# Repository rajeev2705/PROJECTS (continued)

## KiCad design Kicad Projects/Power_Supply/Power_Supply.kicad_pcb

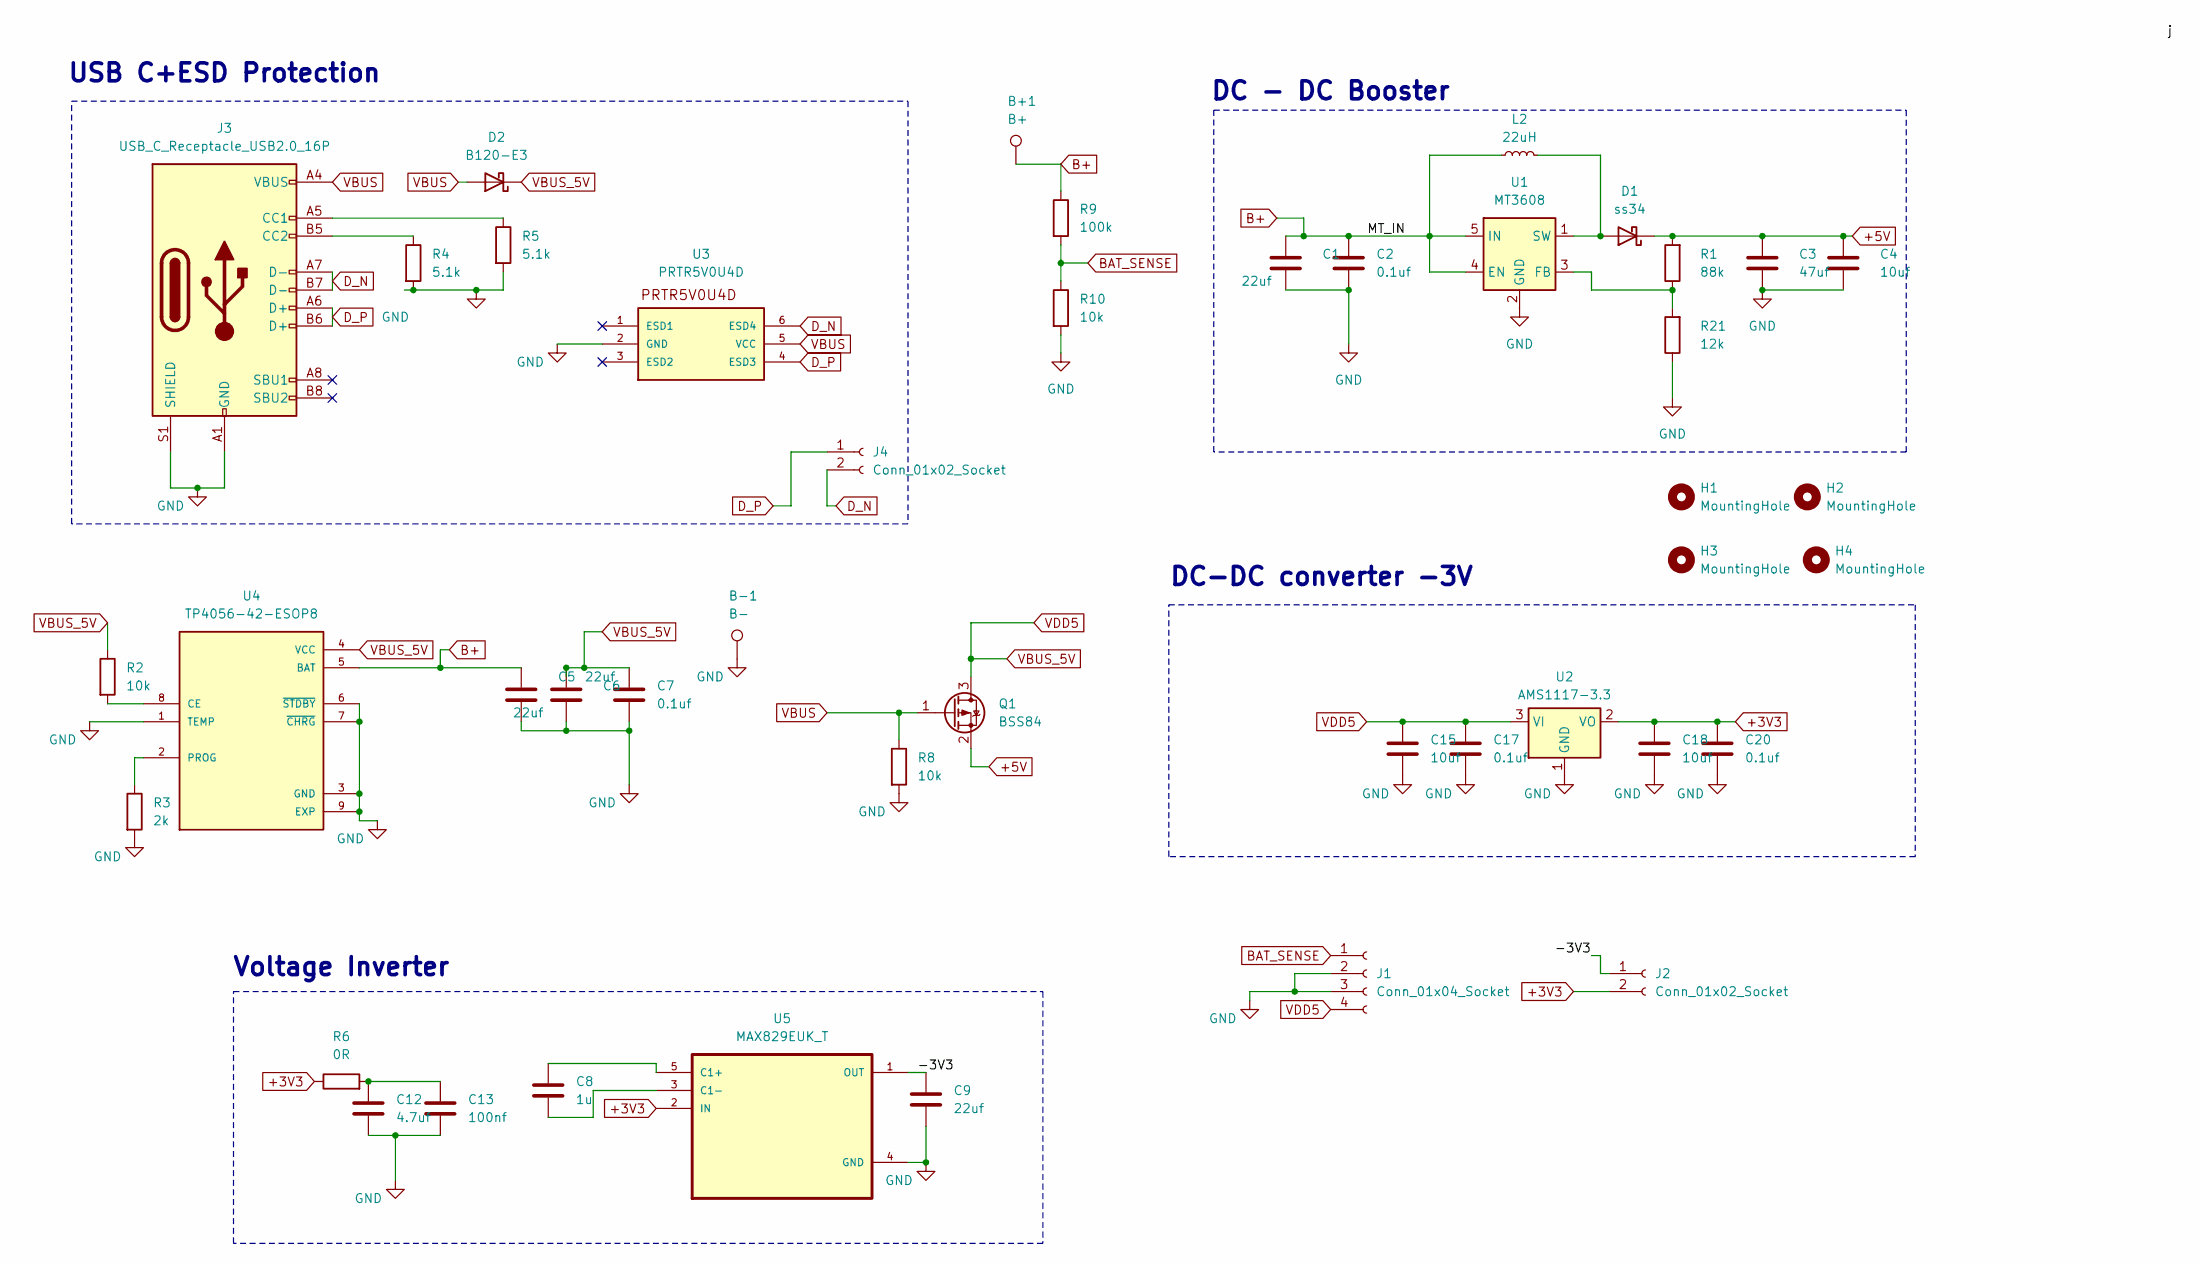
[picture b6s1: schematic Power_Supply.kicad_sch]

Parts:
B+1: B+; TestPoint_Loop_D2.54mm_Drill1.5mm_Beaded
B-1: B-; TestPoint_Loop_D2.54mm_Drill1.5mm_Beaded
C1, C5, C6, C9: 22uf; C_0805_2012Metric_Pad1.18x1.45mm_HandSolder
C2, C7, C17, C20: 0.1uf; C_0805_2012Metric_Pad1.18x1.45mm_HandSolder
C3: 47uf; C_0805_2012Metric_Pad1.18x1.45mm_HandSolder
C4, C15, C18: 10uf; C_0805_2012Metric_Pad1.18x1.45mm_HandSolder
C8: 1u; C_0805_2012Metric_Pad1.18x1.45mm_HandSolder
C12: 4.7uf; C_0805_2012Metric_Pad1.18x1.45mm_HandSolder
C13: 100nf; C_0805_2012Metric_Pad1.18x1.45mm_HandSolder
D1: ss34; D_SMA
D2: B120-E3; D_SMA
H1, H2, H3, H4: MountingHole; MountingHole_2.5mm
J1: Conn_01x04_Socket; PinSocket_1x04_P2.54mm_Vertical
J2, J4: Conn_01x02_Socket; PinSocket_1x02_P2.54mm_Vertical
J3: USB_C_Receptacle_USB2.0_16P; USB_C_Receptacle_HRO_TYPE-C-31-M-12
L2: 22uH; L_TDK_SLF10165
Q1: BSS84; SOT-23
R1: 88k; R_0805_2012Metric_Pad1.20x1.40mm_HandSolder
R2, R8, R10: 10k; R_0805_2012Metric_Pad1.20x1.40mm_HandSolder
R3: 2k; R_0805_2012Metric_Pad1.20x1.40mm_HandSolder
R4, R5: 5.1k; R_0805_2012Metric_Pad1.20x1.40mm_HandSolder
R6: 0R; R_0805_2012Metric_Pad1.20x1.40mm_HandSolder
R9: 100k; R_0805_2012Metric_Pad1.20x1.40mm_HandSolder
R21: 12k; R_0805_2012Metric_Pad1.20x1.40mm_HandSolder
U1: MT3608; SOT-23-6
U2: AMS1117-3.3; SOT-223-3_TabPin2
U3: PRTR5V0U4D; ROHM_SOT-457_ClockwisePinNumbering
U4: TP4056-42-ESOP8; SOIC127P600X175-9N; PARTREV NA
U5: MAX829EUK_T; SOT95P280X145-5N

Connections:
+3V3: C18.1, C20.1, J2.2, R6.1, U2.2 (VO), U5.2 (IN)
+5V: C3.1, C4.1, D1.1 (K), Q1.2 (S), R1.2
/-3V3: C9.1, J2.1, U5.1 (OUT)
B+: B+1.1, C1.1, C2.1, C5.1, L2.2, R9.1, U1.4 (EN), U1.5 (IN), U4.5 (BAT)
BAT_SENSE: J1.1, R9.2, R10.1
D_N: J3.A7 (D-), J3.B7 (D-), J4.2, U3.6 (ESD4)
D_P: J3.A6 (D+), J3.B6 (D+), J4.1, U3.4 (ESD3)
GND: B-1.1, C1.2, C2.2, C3.2, C4.2, C5.2, C6.2, C7.2, C9.2, C12.2, C13.2, C15.2, C17.2, C18.2, C20.2, J1.2, J1.3, J3.A1 (GND), J3.A12 (GND), J3.B1 (GND), J3.B12 (GND), J3.S1 (SHIELD), R3.2, R4.2, R5.2, R8.2, R10.2, R21.1, U1.2 (GND), U2.1 (GND), U3.2 (GND), U4.1 (TEMP), U4.3 (GND), U4.6 (~STDBY), U4.7 (~CHRG), U4.9 (EXP), U5.4 (GND)
unnamed: C12.1, C13.1, R6.2
unnamed: D1.2 (A), L2.1, U1.1 (SW)
unnamed: J3.A5 (CC1), R5.1
unnamed: J3.B5 (CC2), R4.1
unnamed: R1.1, R21.2, U1.3 (FB)
unnamed: R2.2, U4.8 (CE)
unnamed: R3.1, U4.2 (PROG)
unnamed: C8.1, U5.5 (C1+)
unnamed: C8.2, U5.3 (C1-)
VBUS: D2.2 (A), J3.A4 (VBUS), J3.A9 (VBUS), J3.B4 (VBUS), J3.B9 (VBUS), Q1.1 (G), R8.1, U3.5 (VCC)
VBUS_5V: C6.1, C7.1, C15.1, C17.1, D2.1 (K), J1.4, Q1.3 (D), R2.1, U2.3 (VI), U4.4 (VCC)

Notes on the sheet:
DC - DC Booster
USB C+ESD Protection
DC-DC converter -3V
Voltage Inverter

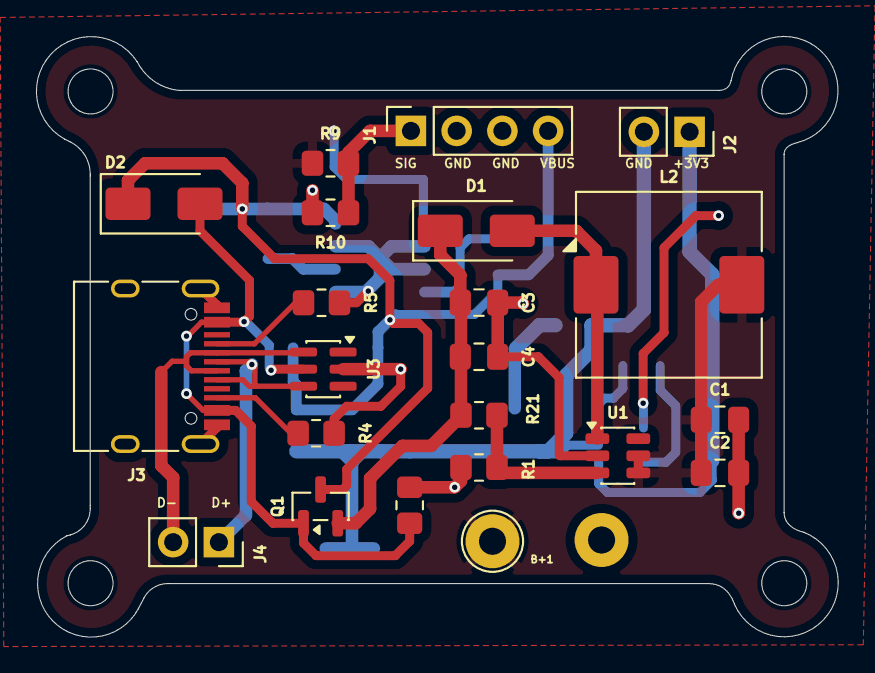
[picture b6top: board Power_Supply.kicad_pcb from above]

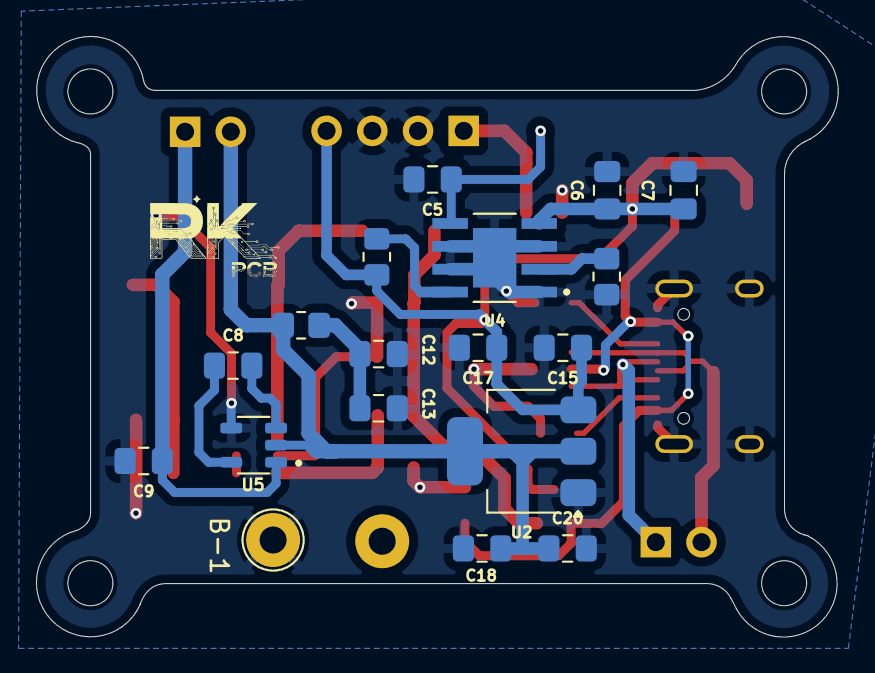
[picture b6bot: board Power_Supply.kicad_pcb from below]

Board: 2 copper layers, 44.5 x 33.4 mm, 44 parts (18 on the bottom side), 19 nets.

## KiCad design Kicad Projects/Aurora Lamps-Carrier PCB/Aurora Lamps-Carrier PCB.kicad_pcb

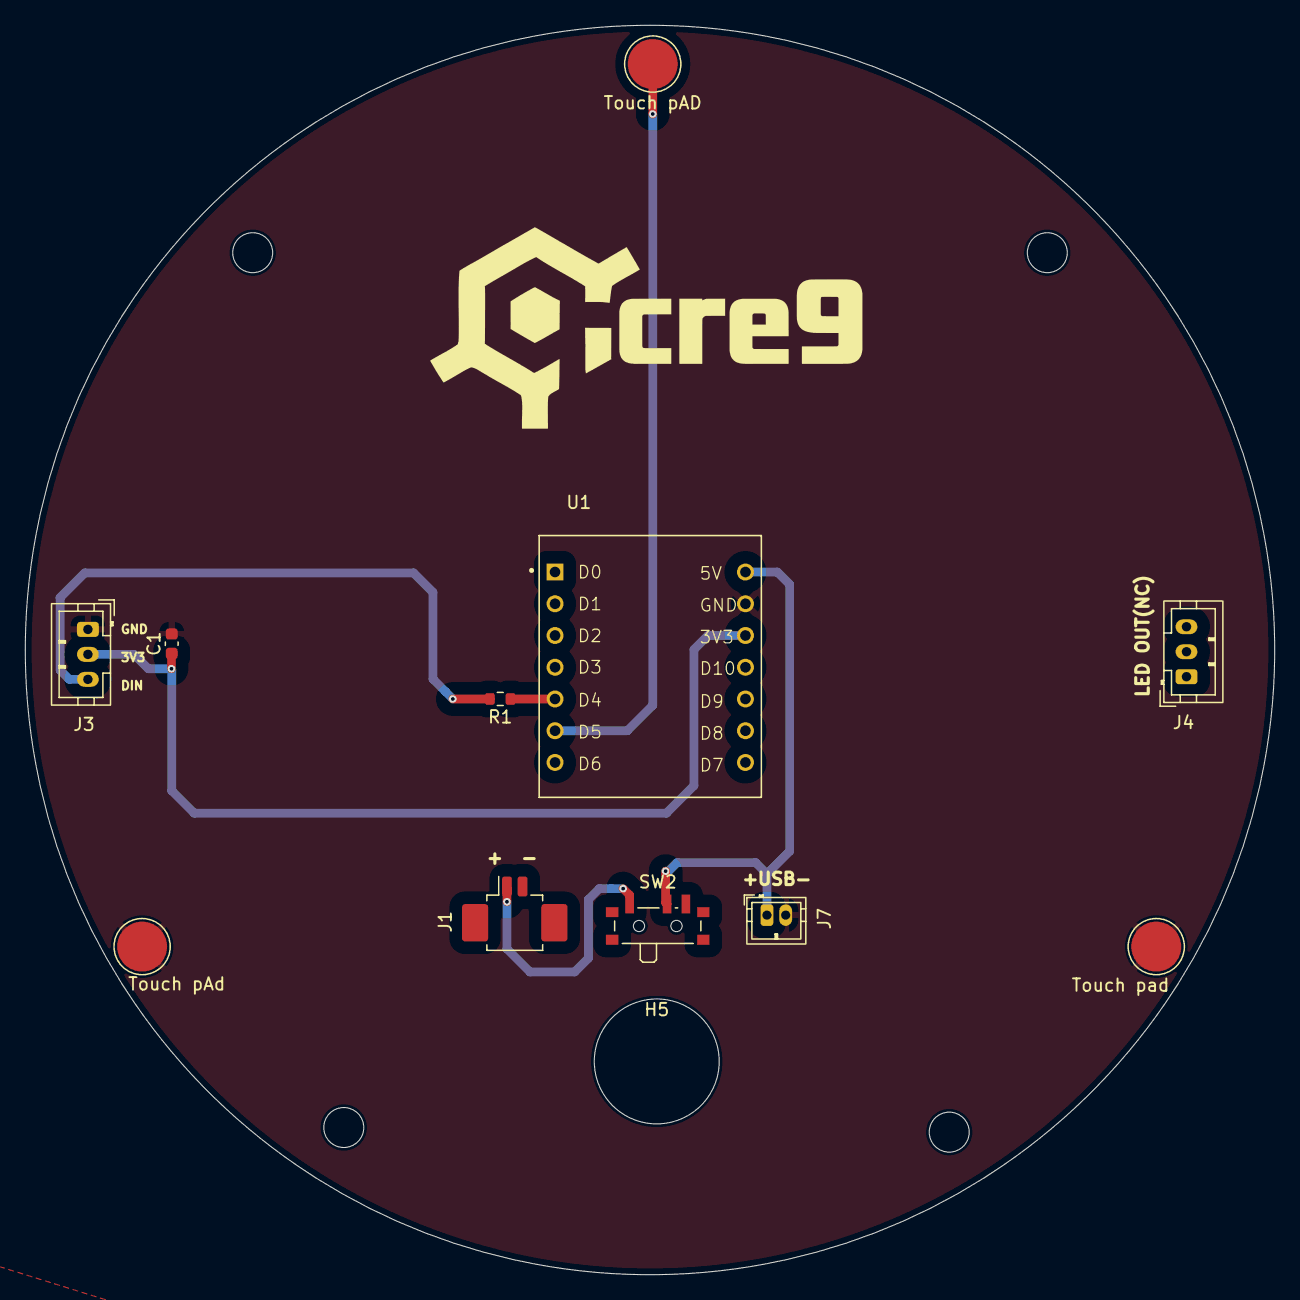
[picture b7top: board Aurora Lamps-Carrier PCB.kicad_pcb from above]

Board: 2 copper layers, 100.0 x 100.0 mm, 16 parts (0 on the bottom side), 7 nets.

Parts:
C1: 100nf; C_0603_1608Metric
H1, H2, H3, H4, H5: MountingHole; MountingHole_3.2mm_M3
J1: BATTERY; Molex_PicoBlade_53261-0271_1x02-1MP_P1.25mm_Horizontal
J2: Touch pAD; TestPoint_Pad_D4.0mm
J3: LED Connector; JST_PH_B3B-PH-K_1x03_P2.00mm_Vertical
J4: led ring out; JST_PH_B3B-PH-K_1x03_P2.00mm_Vertical
J5: Touch pad; TestPoint_Pad_D4.0mm
J6: Touch pAd; TestPoint_Pad_D4.0mm
J7: USBPower EXt; JST_ZH_B2B-ZR_1x02_P1.50mm_Vertical
R1: 330R; R_0603_1608Metric
SW2: SW_SPDT; SW_SPDT_PCM12
U1: XIAO_ESP32S3; MODULE_XIAO_ESP32C3

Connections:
B+: J1.1, SW2.1 (A)
BAT+: J7.1, SW2.2 (B), U1.14 (VUSB)
GND: C1.2, J3.1, J5.1, J6.1, J7.2, U1.13 (GND)
LED_DATA: R1.1, U1.5 (D4)
MCU_3V3: C1.1, J3.2, U1.12 (VCC_3V3)
unnamed: J3.3, R1.2
TOUCH: J2.1, U1.6 (D5)

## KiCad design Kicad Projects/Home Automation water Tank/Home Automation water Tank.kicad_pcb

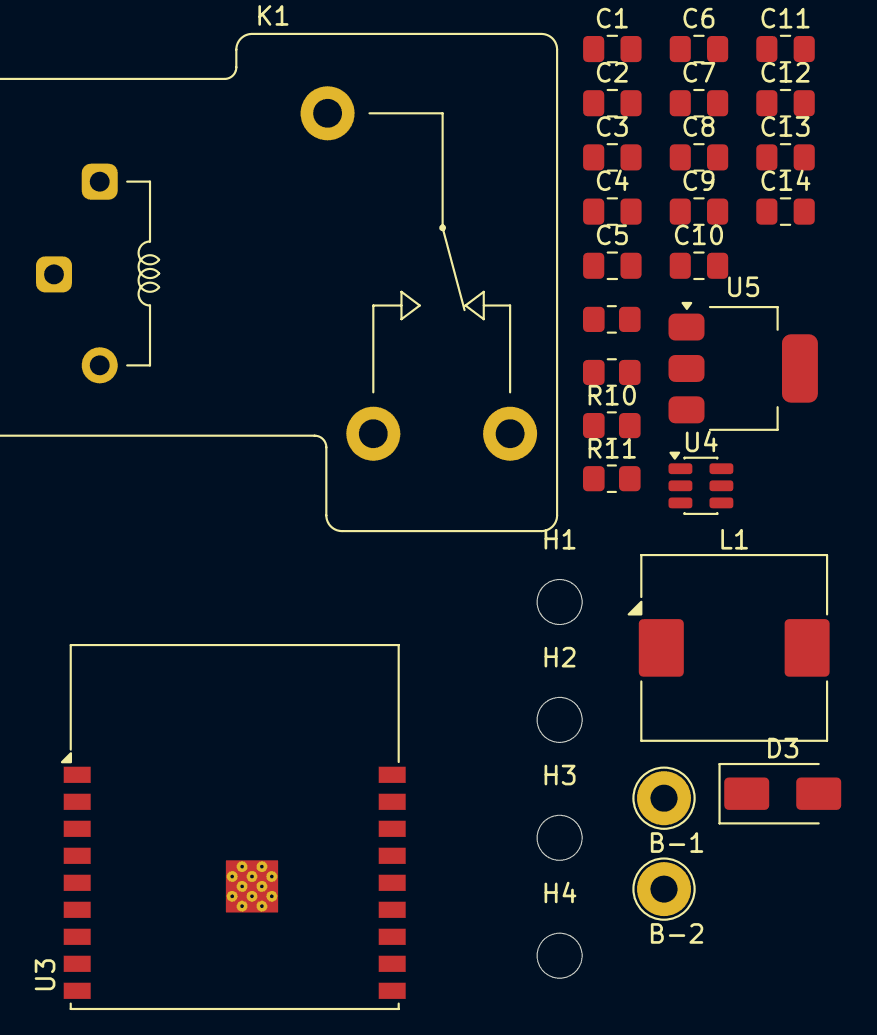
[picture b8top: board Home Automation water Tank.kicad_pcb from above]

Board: 2 copper layers, 30 parts (0 on the bottom side), 8 nets, no tracks yet.

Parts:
B-1: B-; TestPoint_Loop_D2.54mm_Drill1.5mm_Beaded
B-2: B+; TestPoint_Loop_D2.54mm_Drill1.5mm_Beaded
C1, C2, C5: 22uf; C_0805_2012Metric_Pad1.18x1.45mm_HandSolder
C3, C7: 0.1uf; C_0805_2012Metric_Pad1.18x1.45mm_HandSolder
C4, C8, C9, C12, C13: 47uf; C_0805_2012Metric_Pad1.18x1.45mm_HandSolder
C6, C10, C11, C14: 10uf; C_0805_2012Metric_Pad1.18x1.45mm_HandSolder
D3: ss34; D_SMA
H1, H2, H3, H4: MountingHole; MountingHole_2.5mm
K1: RAYEX-L90S; Relay_SPDT_RAYEX-L90S
L1: 22uH; L_TDK_SLF10165
R6: 10k; R_0805_2012Metric_Pad1.20x1.40mm_HandSolder
R7: 2k; R_0805_2012Metric_Pad1.20x1.40mm_HandSolder
R10: 88k; R_0805_2012Metric_Pad1.20x1.40mm_HandSolder
R11: 12k; R_0805_2012Metric_Pad1.20x1.40mm_HandSolder
U3: ESP32-C3-WROOM-02
U4: MT3608; SOT-23-6
U5: AMS1117-3.3; SOT-223-3_TabPin2

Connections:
+3V3: C4.1, C6.1, C13.1, C14.1, U3.1 (3V3), U5.2 (VO)
+6V: C9.1, C10.1, C11.1, C12.1, D3.1 (K), R10.2, U5.3 (VI)
/MCU_EN: C8.2, U3.2 (EN)
B+: B-2.1, C1.1, C5.1, C7.1, L1.2, U4.4 (EN), U4.5 (IN)
GND: B-1.1, C1.2, C2.2, C3.2, C4.2, C5.2, C6.2, C7.2, C8.1, C9.2, C10.2, C11.2, C12.2, C13.2, C14.2, R7.2, R11.1, U3.9 (GND), U3.19 (GND), U4.2 (GND), U5.1 (GND)
unnamed: D3.2 (A), L1.1, U4.1 (SW)
unnamed: R10.1, R11.2, U4.3 (FB)
USB_5V: C2.1, C3.1, R6.1

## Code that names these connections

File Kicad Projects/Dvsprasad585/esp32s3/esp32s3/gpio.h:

/*----------------------------------------------------------------
 *
 * gpio.h
 *
 * Header file for GPIO functions
 * VSKTarget - ESP32-S3 Port (Rev 6.2)
 *
 * ESP32-S3-WROOM-1 Pin Mapping
 * Based on freETarget v5.2 architecture
 *
 * FULL SIGNAL CHAIN (Rev 6.2):
 *   - Filter network (10K + 10nF slope comp) on main board
 *   - 2x LM339 quad comparators on main board
 *   - 4x 74HC74 D flip-flop RUN latches on main board
 *   - ESP32-S3 ISR captures comparator output timestamps
 *   - PCNT-equivalent timing via esp_timer_get_time()
 *   - Sensor daughter boards: Piezo + OPA1641 only
 *   - A0505XT-1WR3-TR isolated ±5V for analog
 *
 * Signal Chain:
 *   Daughter Board: Piezo → OPA1641 amp → analog out via FRC
 *   Main Board: FRC → RC Filter → LM339 (vs VREF) → 74HC74 latch
 *               LM339 output also → ESP32-S3 GPIO ISR (timing)
 *               74HC74 Q → ESP32-S3 GPIO (RUN status)
 *
 *---------------------------------------------------------------*/
#ifndef _GPIO_H_
#define _GPIO_H_

#include "driver/pulse_cnt.h"

/*
 * Global functions
 */
void init_gpio(void);
void init_pcnt(void);
void arm_timers(void);
void clear_running(void);
unsigned int is_running(void);
void set_LED(int state_RDY, int state_X, int state_Y);
unsigned int read_DIP(unsigned int dip_mask);
void stop_timers(void);
void trip_timers(void);
bool read_in(unsigned int port);
void read_timers(unsigned int* timer_counts);
void drive_paper(void);
void enable_face_interrupt();
void disable_face_interrupt(void);
void enable_sensor_interrupt();
void disable_sensor_interrupt(void);
void multifunction_init(void);
void multifunction_switch(void);
void multifunction_display(void);
void multifunction_wait_open(void);
void output_to_all(char* s);
void char_to_all(char ch);
void digital_test(void);
void paper_on_off(bool on);
void rapid_green(unsigned int state);
void rapid_red(unsigned int state);
char get_all(void);
char aux_spool_read(void);
int  aux_spool_available(void);
void aux_spool_put(char ch);
char json_spool_read(void);
int  json_spool_available(void);
void json_spool_put(char ch);
void set_vref(unsigned int millivolts);

/*
 *  ESP32-S3 GPIO Pin Allocation (Rev 6.2 - Full Signal Chain)
 *  ==========================================================
 *
 *  Total available GPIOs: 45
 *  Total used: 25
 *  Spare: 20
 *
 *  MAIN BOARD SIGNAL CHAIN:
 *    FRC analog → RF1-RF4 (10K) + CF1-CF4 (10nF) → LM339 → 74HC74
 *    2x LM339 (quad comparator, SOIC-14) powered by +5V_ISO
 *    4x 74HC74 (dual D flip-flop, SOIC-14) powered by +3V3
 *    RP1-RP4 (10K pull-ups) on LM339 open-collector outputs
 *
 *  COMPARATOR OUTPUTS (LM339 → ESP32-S3 ISR for timing):
 *    COMP_N: GPIO4 (LM339 #1 OUT1) → ISR timestamp
 *    COMP_E: GPIO5 (LM339 #1 OUT2) → ISR timestamp
 *    COMP_S: GPIO6 (LM339 #2 OUT1) → ISR timestamp
 *    COMP_W: GPIO7 (LM339 #2 OUT2) → ISR timestamp
 *
 *  RUN LATCHES (74HC74 Q → ESP32-S3 for status polling):
 *    RUN_N: GPIO15 (74HC74 #1 Q1)
 *    RUN_E: GPIO16 (74HC74 #2 Q1)
 *    RUN_S: GPIO17 (74HC74 #3 Q1)
 *    RUN_W: GPIO18 (74HC74 #4 Q1)
 *
 *  LATCH CONTROL:
 *    LATCH_CLR: GPIO38 → 74HC74 /CLR (active low clear)
 *
 *  I2C PERIPHERALS (SDA=GPIO1, SCL=GPIO2):
 *    ADS1115 #1 (0x48): Sensor analog monitoring
 *    ADS1115 #2 (0x49): VREF/battery monitoring
 *    LM75 (0x4F):       Temperature sensor
 */

/*
 * Comparator Outputs (LM339 → ESP32-S3 GPIO)
 * These are the timing-critical inputs - ISR captures timestamp
 * LM339 open-collector with 10K pull-up to +3V3
 */
#define COMP_NORTH    4                    // LM339 #1 OUT1 → GPIO4
#define COMP_EAST     5                    // LM339 #1 OUT2 → GPIO5
#define COMP_SOUTH    6                    // LM339 #2 OUT1 → GPIO6
#define COMP_WEST     7                    // LM339 #2 OUT2 → GPIO7

/*
 * RUN Latch Outputs (74HC74 Q → ESP32-S3 GPIO)
 * Polled by is_running() to check which sensors have fired
 */
#define RUN_NORTH     15                   // 74HC74 #1 Q1 → GPIO15
#define RUN_EAST      16                   // 74HC74 #2 Q1 → GPIO16
#define RUN_SOUTH     17                   // 74HC74 #3 Q1 → GPIO17
#define RUN_WEST      18                   // 74HC74 #4 Q1 → GPIO18

/*
 * Latch Clear (ESP32-S3 → 74HC74 /CLR, active low)
 */
#define LATCH_CLR     38                   // Clear all RUN latches

/*
 * Legacy aliases for compatibility
 */
#define SENSOR_NORTH  COMP_NORTH
#define SENSOR_EAST   COMP_EAST
#define SENSOR_SOUTH  COMP_SOUTH
#define SENSOR_WEST   COMP_WEST

/*
 * LED Outputs (directly on ESP32-S3 GPIO)
 */
#define LED_RDY     47                    // Ready LED (green)
#define LED_X       48                    // X-axis LED (red)
#define LED_Y       45                    // Y-axis LED (yellow)

/*
 * Paper Motor (via 2N7002 MOSFET on GPIO)
 */
#define PAPER       46                    // Paper advance drive

/*
 * Face Sensor (interrupt capable)
 */
#define FACE_SENSOR 11                    // Face strike input

/*
 * Rapid Fire Outputs
 */
#define RAPID_RED_PIN    9                // Rapid fire RED output
#define RAPID_GREEN_PIN 10                // Rapid fire GREEN output

/*
 * Software-Controlled VREF
 * ESP32-S3 LEDC PWM → R7 (10K) + C9 (100nF) RC filter
 * Sent to LM339 inverting inputs as comparator threshold
 * Also sent to daughter boards via FRC pin 9
 */
#define VREF_DAC_PIN  3                   // PWM output for VREF control
#define VREF_CHANNEL  0                   // LEDC channel

/*
 * DIP Switches - controlled via JSON (no physical switches)
 */
#define CALIBRATE       (0)
#define DIP_SW_A        (0)
#define CAL_LOW         (DIP_SW_A)
#define DIP_SW_B        (0)
#define CAL_HIGH        (DIP_SW_B)
#define VERBOSE_TRACE   (0)

/*
 * PWM for LED illumination (using ESP32-S3 LEDC peripheral)
 */
#define LED_PWM_PIN      14               // Spare GPIO for LED strip PWM
#define VSET_PWM_CHANNEL  0               // LEDC channel (shared with VREF)
#define LED_PWM_CHANNEL   1               // LEDC channel
#define PWM_FREQUENCY     5000            // 5 kHz PWM
#define PWM_RESOLUTION    8               // 8-bit resolution (0-255)

#define LON          1
#define LOF          0
#define LXX         -1
#define L(A, B, C)  (A), (B), (C)

#define NORTH        0
#define EAST         1
#define SOUTH        2
#define WEST         3
#define TRIP_NORTH   0x01
#define TRIP_EAST    0x02
#define TRIP_SOUTH   0x04
#define TRIP_WEST    0x08

/*
 * Paper Motor
 */
#define PAPER_ON      1
#define PAPER_OFF     0

/*
 * Serial Port Pins for ESP32-S3
 * USB-CDC  = Native USB (GPIO19/GPIO20) - primary serial
 * UART0    = FT231XS bridge (GPIO43 TX / GPIO44 RX)
 * Serial1  = AUX/Token Ring (GPIO8 TX / GPIO0 RX)
 */
#define AUX_TX_PIN    8
#define AUX_RX_PIN    0

#define DISP_TX_PIN  43                   // UART0 TX (FT231XS)
#define DISP_RX_PIN  44                   // UART0 RX (FT231XS)

/*
 * I2C Bus (DEDICATED - no pin sharing)
 */
#define I2C_SDA       1
#define I2C_SCL       2

/*
 * USB Native (ESP32-S3 USB-OTG)
 */
#define USB_DM       19
#define USB_DP       20

/*
 * PCNT Configuration (timing via ISR + esp_timer)
 * Resolution: 1 microsecond via esp_timer_get_time()
 */
#define PCNT_UNIT_NORTH  0
#define PCNT_UNIT_EAST   1
#define PCNT_UNIT_SOUTH  2
#define PCNT_UNIT_WEST   3

/*
 * Multifunction Switch Use (same as original)
 */
#define HOLD1(x)    LO10((x))
#define HOLD2(x)    HI10((x))
#define TAP1(x)     HLO10((x))
#define TAP2(x)     HHI10((x))
#define HOLD12(x)   HHH10((x))

#define POWER_TAP     0
#define PAPER_FEED    1
#define LED_ADJUST    2
#define PAPER_SHOT    3
#define PC_TEST       4
#define ON_OFF        5
#define MFS_SPARE_6   6
#define MFS_SPARE_7   7
#define MFS_SPARE_8   8
#define TARGET_TYPE   9

#define NO_ACTION     0
#define RAPID_RED     1
#define RAPID_GREEN   2

#define RED_OUT      RAPID_RED_PIN
#define GREEN_OUT    RAPID_GREEN_PIN
#define RED_MASK     1
#define GREEN_MASK   8

#define EOF_MARKER 0xFF

#endif

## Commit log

2026-05-01 Initial commit: overwrite with local Projects folder
2026-05-01 Add and update projects, remove backups and large files
2026-05-01 Secure client folders: keep only portfolios, ignore code and designs
